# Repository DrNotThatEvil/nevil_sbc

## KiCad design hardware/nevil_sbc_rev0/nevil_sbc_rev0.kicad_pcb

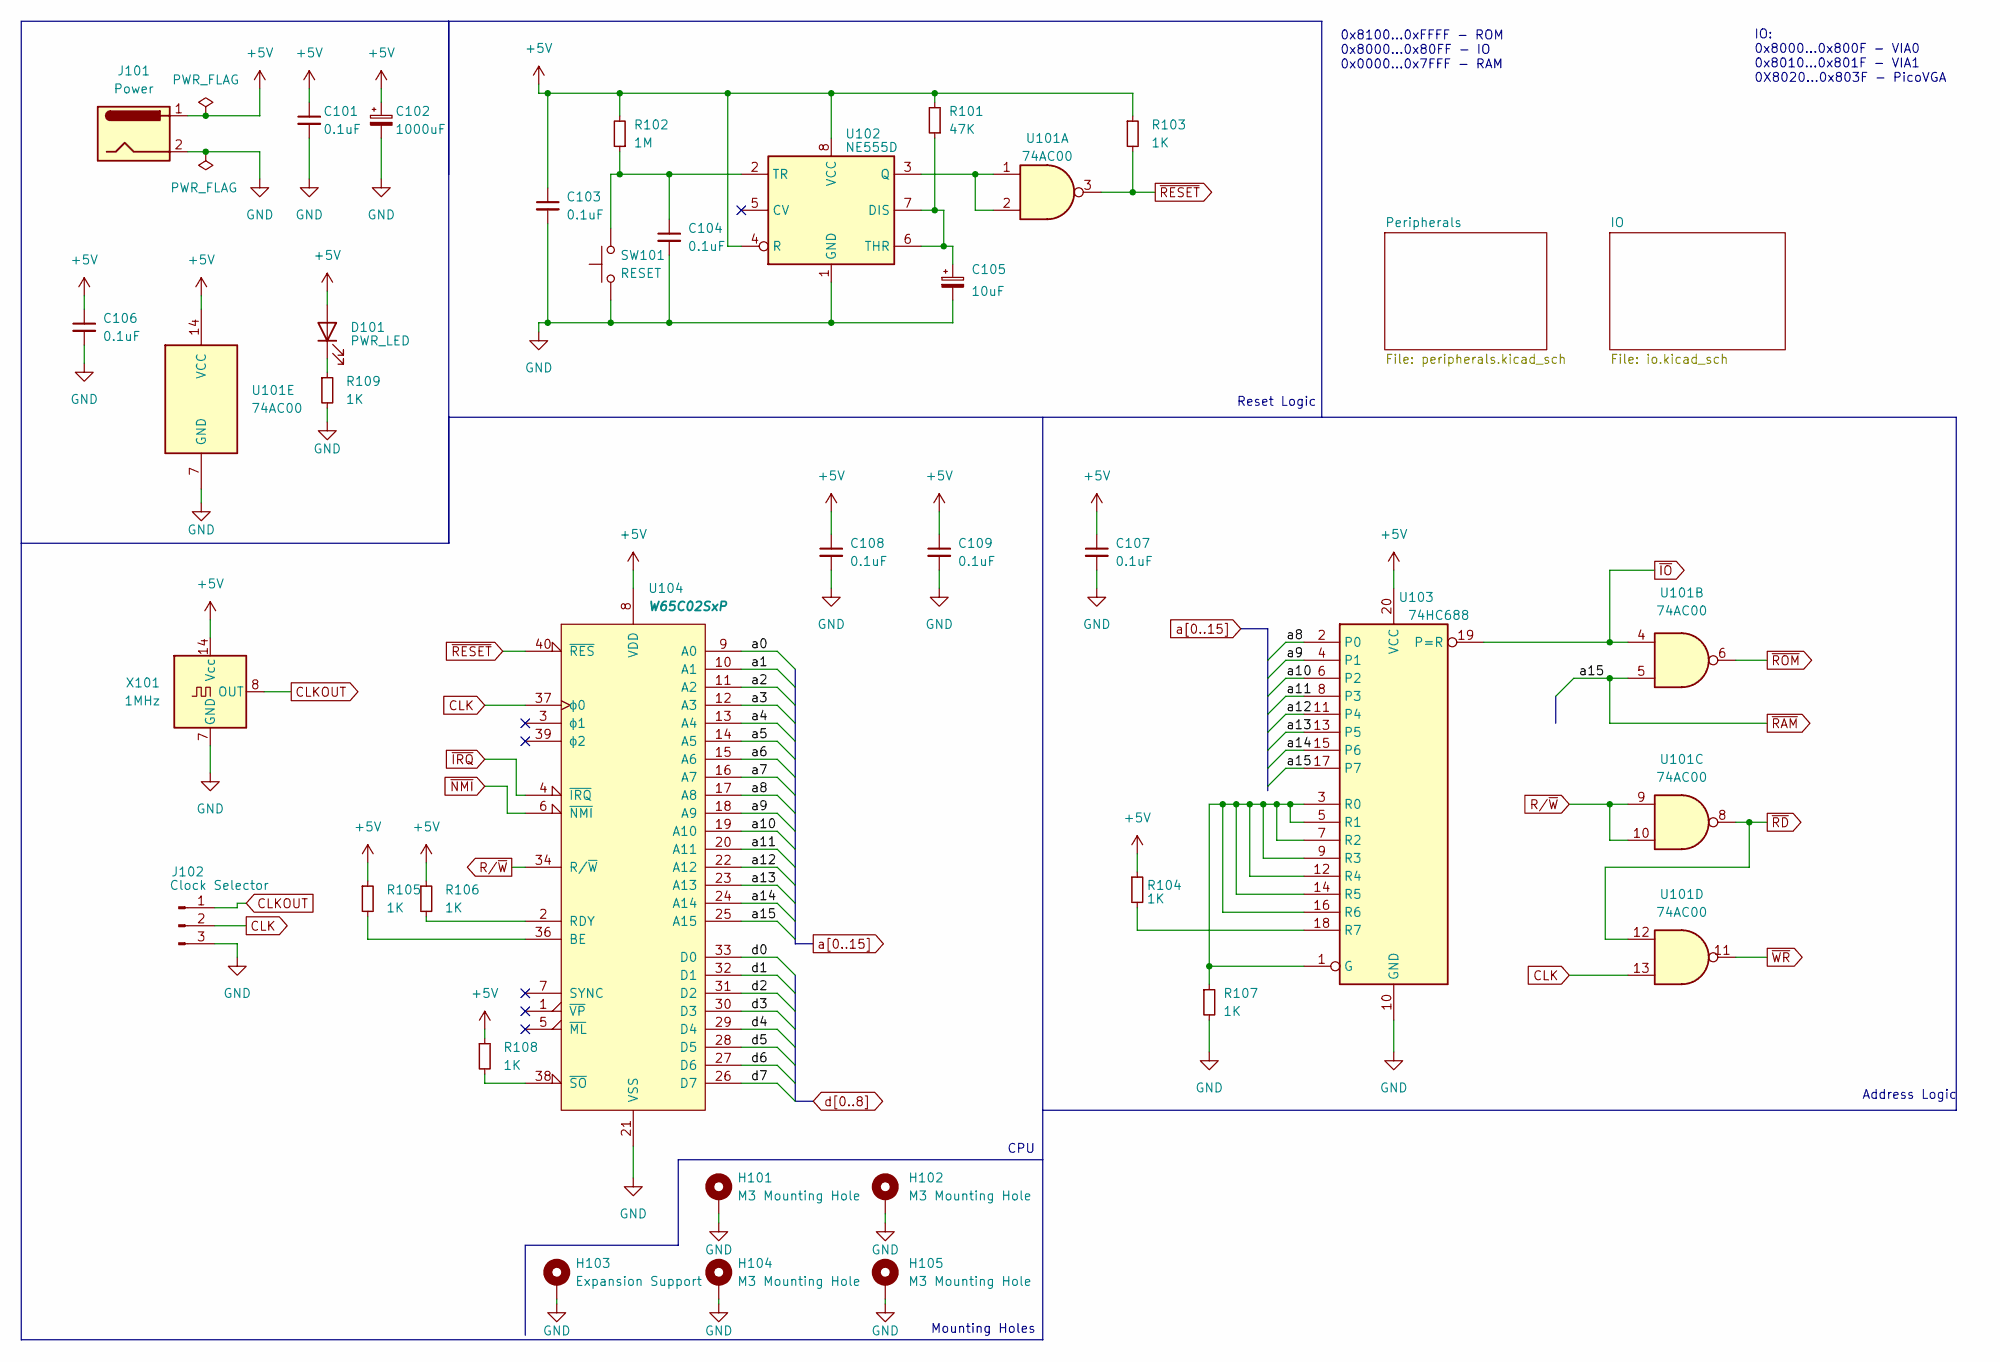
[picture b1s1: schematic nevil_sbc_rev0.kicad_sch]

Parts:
C101, C103, C104, C106, C107, C108, C109: 0.1uF; C_Disc_D5.0mm_W2.5mm_P5.00mm
C102: 1000uF; CP_Radial_D10.0mm_P5.00mm
C105: 10uF; CP_Radial_D5.0mm_P2.00mm
D101: PWR_LED; LED_D3.0mm
H101, H102, H104, H105: M3 Mounting Hole; MountingHole_3.2mm_M3_Pad
H103: Expansion Support; MountingHole_3.2mm_M3_Pad
J101: Power; C9743-CCRNB001R
J102: Clock Selector; PinHeader_1x03_P2.54mm_Vertical
R101: 47K; R_Axial_DIN0204_L3.6mm_D1.6mm_P7.62mm_Horizontal
R102: 1M; R_Axial_DIN0204_L3.6mm_D1.6mm_P7.62mm_Horizontal
R103, R104, R105, R106, R107, R108, R109: 1K; R_Axial_DIN0204_L3.6mm_D1.6mm_P7.62mm_Horizontal
SW101: RESET; SW_PUSH_6mm
U101: 74AC00; DIP-14_W7.62mm_Socket_LongPads
U102: NE555D; SO-8_5.3x6.2mm_P1.27mm
U103: 74HC688; DIP-20_W7.62mm_Socket_LongPads
U104: W65C02SxP; DIP-40_W15.24mm_Socket_LongPads
X101: 1MHz; DIP-14_W7.62mm_Socket_LongPads

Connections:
+5V: C101.1, C102.1, C103.1, C106.1, C107.1, C108.1, C109.1, D101.2 (A), J101.1, R101.2, R102.2, R103.1, R104.1, R105.1, R106.1, R108.1, U101.14 (VCC), U102.4 (R), U102.8 (VCC), U103.20 (VCC), U104.8 (VDD), X101.14 (Vcc); also elsewhere on the board
CLK: J102.2, U101.13, U104.37 (ϕ0); also elsewhere on the board
CLKOUT: J102.1, X101.8 (OUT)
GND: C101.2, C102.2, C103.2, C104.2, C105.2, C106.2, C107.2, C108.2, C109.2, H101.1, H102.1, H103.1, H104.1, H105.1, J101.2, J102.3, R107.2, R109.2, SW101.1, U101.7 (GND), U102.1 (GND), U103.10 (GND), U104.21 (VSS), X101.7 (GND); also elsewhere on the board
unnamed: C104.1, R102.1, SW101.2, U102.2 (TR)
unnamed: C105.1, R101.1, U102.6 (THR), U102.7 (DIS)
unnamed: D101.1 (K), R109.1
unnamed: R104.2, U103.18 (R7)
unnamed: R105.2, U104.36 (BE)
unnamed: R106.2, U104.2 (RDY)
unnamed: R107.1, U103.1 (G), U103.3 (R0), U103.5 (R1), U103.7 (R2), U103.9 (R3), U103.12 (R4), U103.14 (R5), U103.16 (R6)
unnamed: R108.2, U104.38 (~SO)
unnamed: U101.1, U101.2, U102.3 (Q)
R/~W: U101.9, U101.10, U104.34 (R/~W); also elsewhere on the board
a0: U104.9 (A0); also elsewhere on the board
a1: U104.10 (A1); also elsewhere on the board
a2: U104.11 (A2); also elsewhere on the board
a3: U104.12 (A3); also elsewhere on the board
a4: U104.13 (A4); also elsewhere on the board
a5: U104.14 (A5); also elsewhere on the board
a6: U104.15 (A6); also elsewhere on the board
a7: U104.16 (A7); also elsewhere on the board
a8: U103.2 (P0), U104.17 (A8); also elsewhere on the board
a9: U103.4 (P1), U104.18 (A9); also elsewhere on the board
a10: U103.6 (P2), U104.19 (A10); also elsewhere on the board
a11: U103.8 (P3), U104.20 (A11); also elsewhere on the board
a12: U103.11 (P4), U104.22 (A12); also elsewhere on the board
a13: U103.13 (P5), U104.23 (A13); also elsewhere on the board
a14: U103.15 (P6), U104.24 (A14); also elsewhere on the board
d0: U104.33 (D0); also elsewhere on the board
d1: U104.32 (D1); also elsewhere on the board
d2: U104.31 (D2); also elsewhere on the board
d3: U104.30 (D3); also elsewhere on the board
d4: U104.29 (D4); also elsewhere on the board
d5: U104.28 (D5); also elsewhere on the board
d6: U104.27 (D6); also elsewhere on the board
d7: U104.26 (D7); also elsewhere on the board
~IO: U101.4, U103.19 (P=R); also elsewhere on the board
~IRQ: U104.4 (~IRQ); also elsewhere on the board
~NMI: U104.6 (~NMI)
~RAM: U101.5, U103.17 (P7), U104.25 (A15); also elsewhere on the board
~RD: U101.8, U101.12; also elsewhere on the board
~RESET: R103.2, U101.3, U104.40 (~RES); also elsewhere on the board
~ROM: U101.6; also elsewhere on the board
~WR: U101.11; also elsewhere on the board

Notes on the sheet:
CPU
Address Logic
Reset Logic
0x8100...0xFFFF - ROM 0x8000...0x80FF - IO 0x0000...0x7FFF - RAM
IO: 0x8000...0x800F - VIA0 0x8010...0x801F - VIA1 0X8020...0x803F - PicoVGA
Mounting Holes

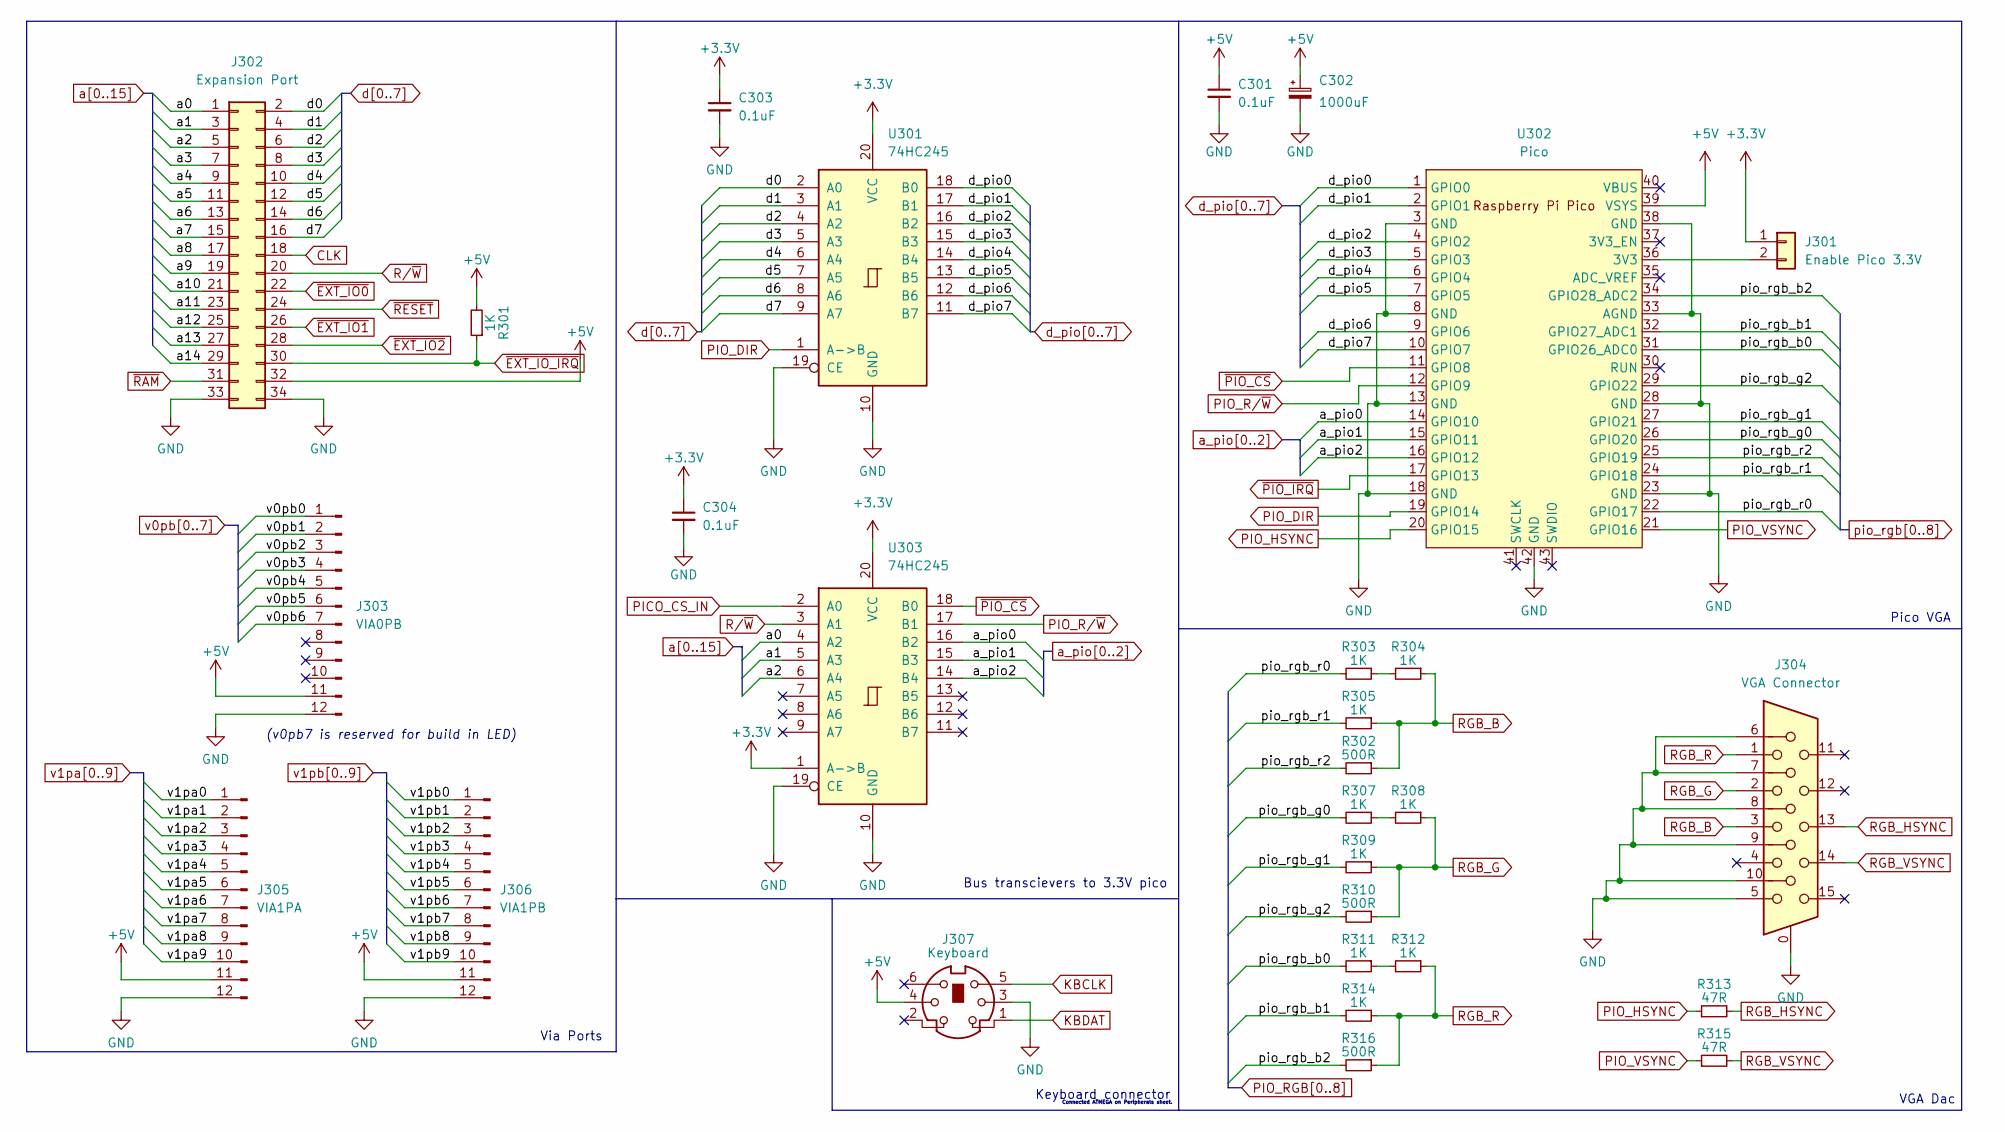
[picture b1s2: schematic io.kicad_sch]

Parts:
C301, C303, C304: 0.1uF; C_Disc_D5.0mm_W2.5mm_P5.00mm
C302: 1000uF; CP_Radial_D10.0mm_P5.00mm
J301: Enable Pico 3.3V; PinHeader_1x02_P2.54mm_Vertical
J302: Expansion Port; PinHeader_2x17_P2.54mm_Vertical
J303: VIA0PB; PinHeader_1x12_P2.54mm_Vertical
J304: VGA Connector; DSUB-15-HD_Female_Horizontal_P2.29x1.98mm_EdgePinOffset8.35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
J305: VIA1PA; PinHeader_1x12_P2.54mm_Vertical
J306: VIA1PB; PinHeader_1x12_P2.54mm_Vertical
J307: Keyboard; TM 0508 A_6
R301, R303, R304, R305, R307, R308, R309, R311, R312, R314: 1K; R_Axial_DIN0204_L3.6mm_D1.6mm_P7.62mm_Horizontal
R302, R310, R316: 500R; R_Axial_DIN0204_L3.6mm_D1.6mm_P7.62mm_Horizontal
R313, R315: 47R; R_Axial_DIN0204_L3.6mm_D1.6mm_P7.62mm_Horizontal
U301, U303: 74HC245; DIP-20_W7.62mm_Socket_LongPads
U302: Pico; RPi_Pico_SMD_TH

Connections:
+3.3V: C303.1, C304.1, J301.1, U301.20 (VCC), U303.1 (A->B), U303.20 (VCC)
+5V: C301.1, C302.1, J302.32, J303.11, J305.11, J306.11, J307.4, R301.2, U302.39 (VSYS); also elsewhere on the board
/IO/pio_rgb_b0: R311.2, U302.31 (GPIO26_ADC0)
/IO/pio_rgb_b1: R314.2, U302.32 (GPIO27_ADC1)
/IO/pio_rgb_b2: R316.2, U302.34 (GPIO28_ADC2)
/IO/pio_rgb_g0: R307.2, U302.26 (GPIO20)
/IO/pio_rgb_g1: R309.2, U302.27 (GPIO21)
/IO/pio_rgb_g2: R310.2, U302.29 (GPIO22)
/IO/pio_rgb_r0: R303.2, U302.22 (GPIO17)
/IO/pio_rgb_r1: R305.2, U302.24 (GPIO18)
/IO/pio_rgb_r2: R302.2, U302.25 (GPIO19)
CLK: J302.18; also elsewhere on the board
GND: C301.2, C302.2, C303.2, C304.2, J302.33, J302.34, J303.12, J304.0, J304.5, J304.6, J304.7, J304.8, J304.9, J304.10, J305.12, J306.12, J307.3, U301.10 (GND), U301.19 (CE), U302.3 (GND), U302.8 (GND), U302.13 (GND), U302.18 (GND), U302.23 (GND), U302.28 (GND), U302.33 (AGND), U302.38 (GND), U302.42 (GND), U303.10 (GND), U303.19 (CE); also elsewhere on the board
KBCLK: J307.5; also elsewhere on the board
KBDAT: J307.1; also elsewhere on the board
unnamed: J301.2, U302.36 (3V3)
unnamed: R303.1, R304.2
unnamed: R307.1, R308.2
unnamed: R311.1, R312.2
PICO_CS_IN: U303.2 (A0); also elsewhere on the board
PIO_DIR: U301.1 (A->B), U302.19 (GPIO14)
PIO_HSYNC: R313.1, U302.20 (GPIO15)
PIO_R/~W: U302.12 (GPIO9), U303.17 (B1)
PIO_VSYNC: R315.1, U302.21 (GPIO16)
RGB_B: J304.3, R302.1, R304.1, R305.1
RGB_G: J304.2, R308.1, R309.1, R310.1
RGB_HSYNC: J304.13, R313.2
RGB_R: J304.1, R312.1, R314.1, R316.1
RGB_VSYNC: J304.14, R315.2
R/~W: J302.20, U303.3 (A1); also elsewhere on the board
a0: J302.1, U303.4 (A2); also elsewhere on the board
a1: J302.3, U303.5 (A3); also elsewhere on the board
a2: J302.5, U303.6 (A4); also elsewhere on the board
a3: J302.7; also elsewhere on the board
a4: J302.9; also elsewhere on the board
a5: J302.11; also elsewhere on the board
a6: J302.13; also elsewhere on the board
a7: J302.15; also elsewhere on the board
a8: J302.17; also elsewhere on the board
a9: J302.19; also elsewhere on the board
a10: J302.21; also elsewhere on the board
a11: J302.23; also elsewhere on the board
a12: J302.25; also elsewhere on the board
a13: J302.27; also elsewhere on the board
a14: J302.29; also elsewhere on the board
a_pio0: U302.14 (GPIO10), U303.16 (B2)
a_pio1: U302.15 (GPIO11), U303.15 (B3)
a_pio2: U302.16 (GPIO12), U303.14 (B4)
d0: J302.2, U301.2 (A0); also elsewhere on the board
d1: J302.4, U301.3 (A1); also elsewhere on the board
d2: J302.6, U301.4 (A2); also elsewhere on the board
d3: J302.8, U301.5 (A3); also elsewhere on the board
d4: J302.10, U301.6 (A4); also elsewhere on the board
d5: J302.12, U301.7 (A5); also elsewhere on the board
d6: J302.14, U301.8 (A6); also elsewhere on the board
d7: J302.16, U301.9 (A7); also elsewhere on the board
d_pio0: U301.18 (B0), U302.1 (GPIO0)
d_pio1: U301.17 (B1), U302.2 (GPIO1)
d_pio2: U301.16 (B2), U302.4 (GPIO2)
d_pio3: U301.15 (B3), U302.5 (GPIO3)
d_pio4: U301.14 (B4), U302.6 (GPIO4)
d_pio5: U301.13 (B5), U302.7 (GPIO5)
d_pio6: U301.12 (B6), U302.9 (GPIO6)
d_pio7: U301.11 (B7), U302.10 (GPIO7)
v0pb0: J303.1; also elsewhere on the board
v0pb1: J303.2; also elsewhere on the board
v0pb2: J303.3; also elsewhere on the board
v0pb3: J303.4; also elsewhere on the board
v0pb4: J303.5; also elsewhere on the board
v0pb5: J303.6; also elsewhere on the board
v0pb6: J303.7; also elsewhere on the board
v1pa0: J305.1; also elsewhere on the board
v1pa1: J305.2; also elsewhere on the board
v1pa2: J305.3; also elsewhere on the board
v1pa3: J305.4; also elsewhere on the board
v1pa4: J305.5; also elsewhere on the board
v1pa5: J305.6; also elsewhere on the board
v1pa6: J305.7; also elsewhere on the board
v1pa7: J305.8; also elsewhere on the board
v1pa8: J305.9; also elsewhere on the board
v1pa9: J305.10; also elsewhere on the board
v1pb0: J306.1; also elsewhere on the board
v1pb1: J306.2; also elsewhere on the board
v1pb2: J306.3; also elsewhere on the board
v1pb3: J306.4; also elsewhere on the board
v1pb4: J306.5; also elsewhere on the board
v1pb5: J306.6; also elsewhere on the board
v1pb6: J306.7; also elsewhere on the board
v1pb7: J306.8; also elsewhere on the board
v1pb8: J306.9; also elsewhere on the board
v1pb9: J306.10; also elsewhere on the board
~EXT_IO0: J302.22; also elsewhere on the board
~EXT_IO1: J302.26; also elsewhere on the board
~EXT_IO2: J302.28; also elsewhere on the board
~EXT_IO_IRQ: J302.30, R301.1; also elsewhere on the board
~PIO_CS: U302.11 (GPIO8), U303.18 (B0)
~PIO_IRQ: U302.17 (GPIO13)
~RAM: J302.31; also elsewhere on the board
~RESET: J302.24; also elsewhere on the board

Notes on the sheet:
Bus transcievers to 3.3V pico
VGA Dac
Connected ATMEGA on Peripherals sheet.
Via Ports
Keyboard connector
Pico VGA
(v0pb7 is reserved for build in LED)

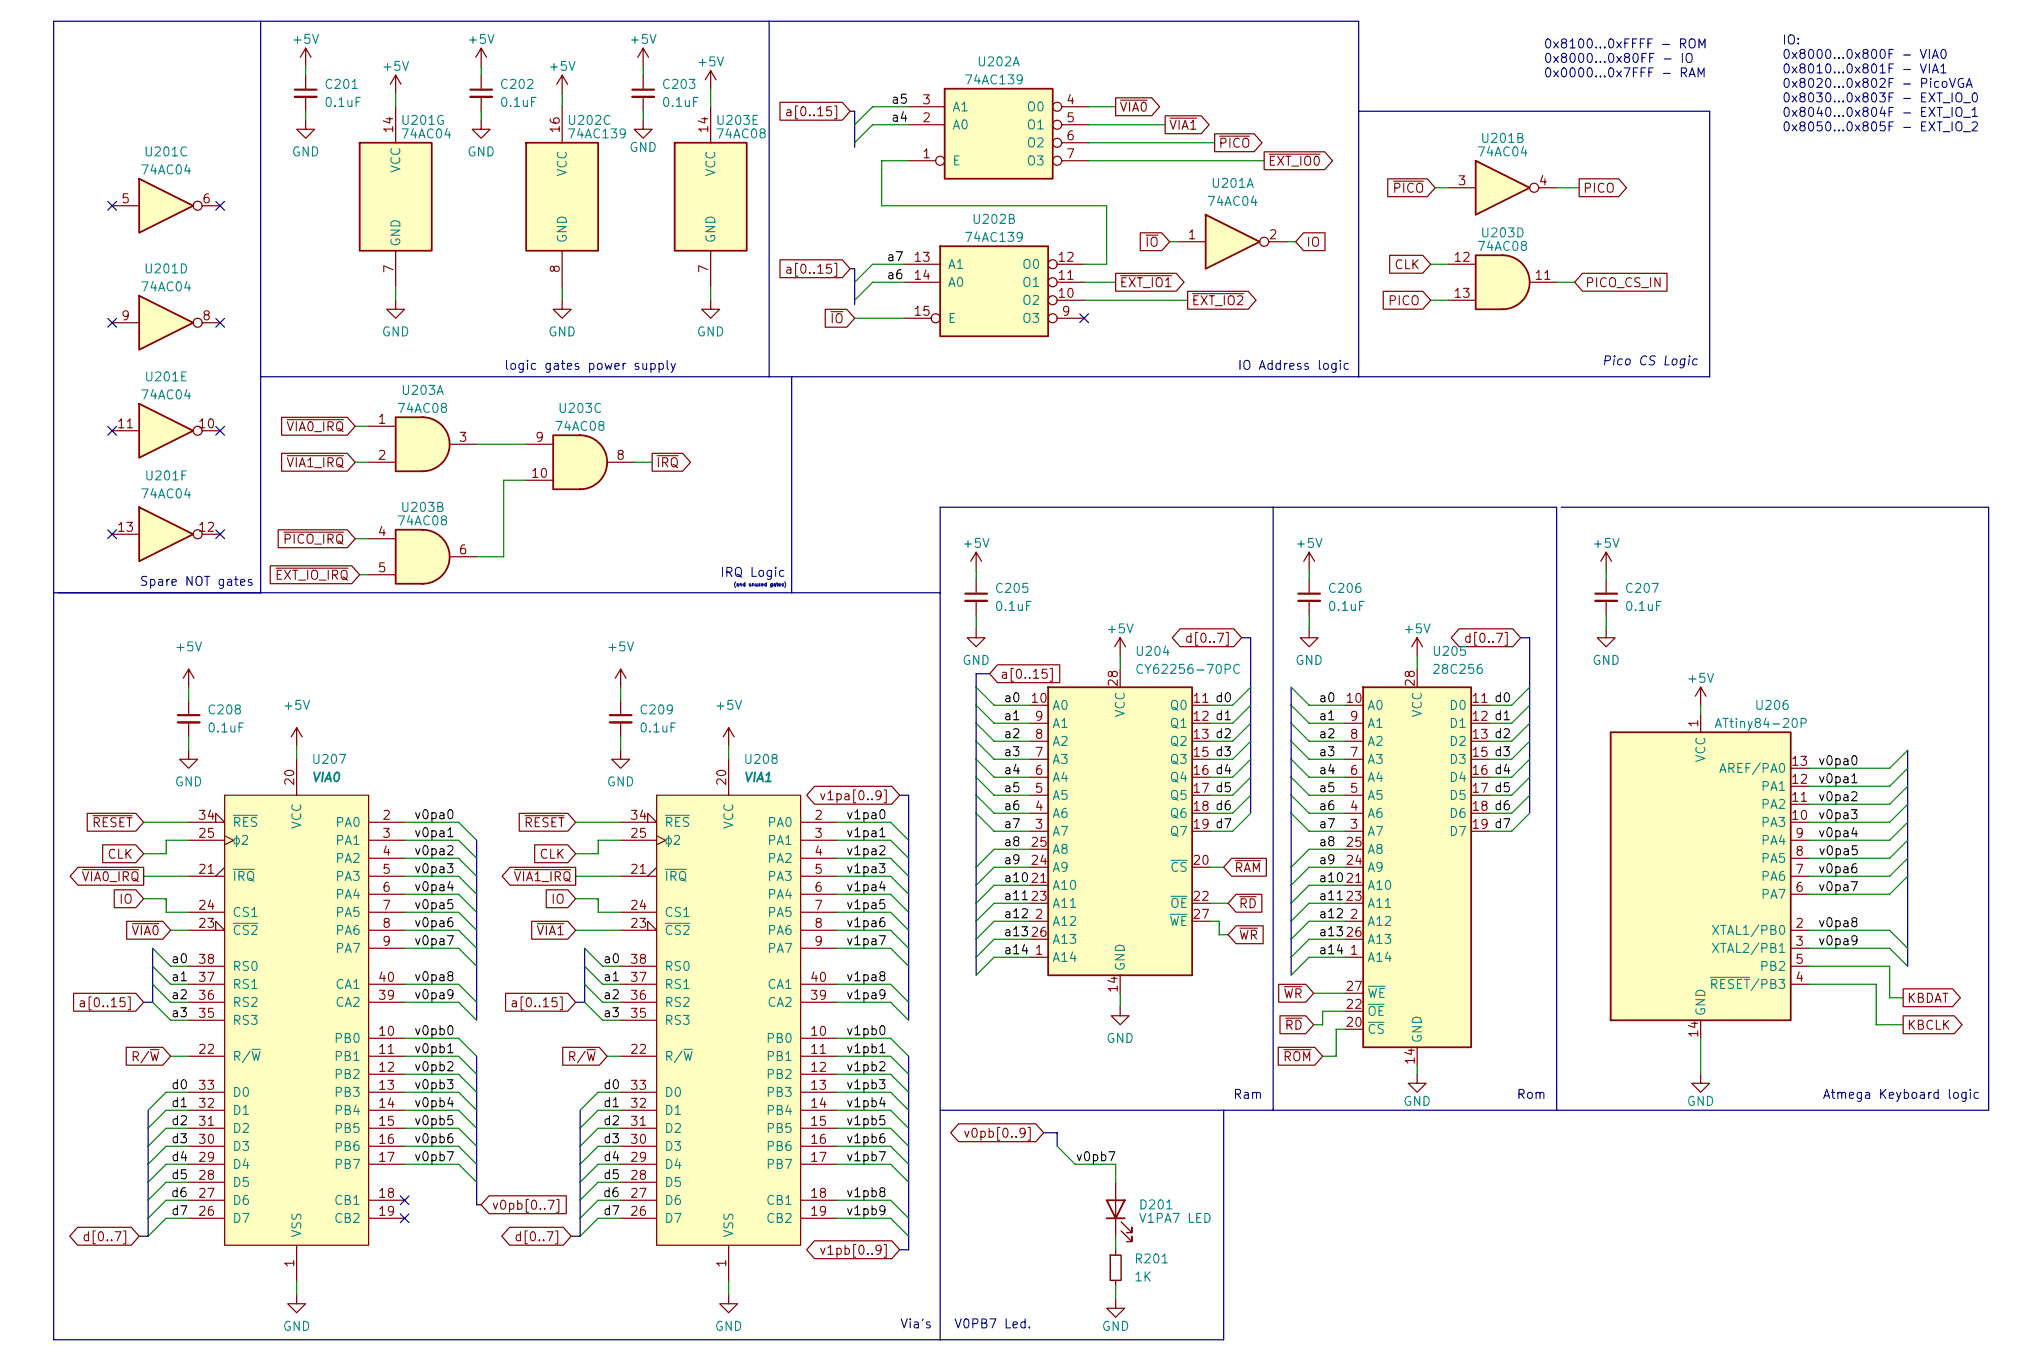
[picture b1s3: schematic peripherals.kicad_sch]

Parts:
C201, C202, C203, C205, C206, C207, C208, C209: 0.1uF; C_Disc_D5.0mm_W2.5mm_P5.00mm
D201: V1PA7 LED; LED_D3.0mm
R201: 1K; R_Axial_DIN0204_L3.6mm_D1.6mm_P7.62mm_Horizontal
U201: 74AC04; DIP-14_W7.62mm_Socket_LongPads
U202: 74AC139; TSSOP-16_4.4x5mm_P0.65mm
U203: 74AC08; DIP-14_W7.62mm_Socket_LongPads
U204: CY62256-70PC; DIP-28_W15.24mm_Socket_LongPads
U205: 28C256; DIP-28_W15.24mm_Socket_LongPads
U206: ATtiny84-20P; DIP-14_W7.62mm
U207: VIA0; DIP-40_W15.24mm_Socket_LongPads
U208: VIA1; DIP-40_W15.24mm_Socket_LongPads

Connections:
+5V: C201.1, C202.1, C203.1, C205.1, C206.1, C207.1, C208.1, C209.1, U201.14 (VCC), U202.16 (VCC), U203.14 (VCC), U204.28 (VCC), U205.28 (VCC), U206.1 (VCC), U207.20 (VCC), U208.20 (VCC); also elsewhere on the board
/Peripherals/v0pa0: U206.13 (AREF/PA0), U207.2 (PA0)
/Peripherals/v0pa1: U206.12 (PA1), U207.3 (PA1)
/Peripherals/v0pa2: U206.11 (PA2), U207.4 (PA2)
/Peripherals/v0pa3: U206.10 (PA3), U207.5 (PA3)
/Peripherals/v0pa4: U206.9 (PA4), U207.6 (PA4)
/Peripherals/v0pa5: U206.8 (PA5), U207.7 (PA5)
/Peripherals/v0pa6: U206.7 (PA6), U207.8 (PA6)
/Peripherals/v0pa7: U206.6 (PA7), U207.9 (PA7)
/Peripherals/v0pa8: U206.2 (XTAL1/PB0), U207.40 (CA1)
/Peripherals/v0pa9: U206.3 (XTAL2/PB1), U207.39 (CA2)
CLK: U203.12, U207.25 (ϕ2), U208.25 (ϕ2); also elsewhere on the board
GND: C201.2, C202.2, C203.2, C205.2, C206.2, C207.2, C208.2, C209.2, R201.2, U201.7 (GND), U202.8 (GND), U203.7 (GND), U204.14 (GND), U205.14 (GND), U206.14 (GND), U207.1 (VSS), U208.1 (VSS); also elsewhere on the board
IO: U201.2, U207.24 (CS1), U208.24 (CS1)
KBCLK: U206.4 (~RESET/PB3); also elsewhere on the board
KBDAT: U206.5 (PB2); also elsewhere on the board
unnamed: D201.1 (K), R201.1
unnamed: U202.1 (E), U202.12 (O0)
unnamed: U203.3, U203.9
unnamed: U203.6, U203.10
PICO: U201.4, U203.13
PICO_CS_IN: U203.11; also elsewhere on the board
R/~W: U207.22 (R/~W), U208.22 (R/~W); also elsewhere on the board
a0: U204.10 (A0), U205.10 (A0), U207.38 (RS0), U208.38 (RS0); also elsewhere on the board
a1: U204.9 (A1), U205.9 (A1), U207.37 (RS1), U208.37 (RS1); also elsewhere on the board
a2: U204.8 (A2), U205.8 (A2), U207.36 (RS2), U208.36 (RS2); also elsewhere on the board
a3: U204.7 (A3), U205.7 (A3), U207.35 (RS3), U208.35 (RS3); also elsewhere on the board
a4: U202.2 (A0), U204.6 (A4), U205.6 (A4); also elsewhere on the board
a5: U202.3 (A1), U204.5 (A5), U205.5 (A5); also elsewhere on the board
a6: U202.14 (A0), U204.4 (A6), U205.4 (A6); also elsewhere on the board
a7: U202.13 (A1), U204.3 (A7), U205.3 (A7); also elsewhere on the board
a8: U204.25 (A8), U205.25 (A8); also elsewhere on the board
a9: U204.24 (A9), U205.24 (A9); also elsewhere on the board
a10: U204.21 (A10), U205.21 (A10); also elsewhere on the board
a11: U204.23 (A11), U205.23 (A11); also elsewhere on the board
a12: U204.2 (A12), U205.2 (A12); also elsewhere on the board
a13: U204.26 (A13), U205.26 (A13); also elsewhere on the board
a14: U204.1 (A14), U205.1 (A14); also elsewhere on the board
d0: U204.11 (Q0), U205.11 (D0), U207.33 (D0), U208.33 (D0); also elsewhere on the board
d1: U204.12 (Q1), U205.12 (D1), U207.32 (D1), U208.32 (D1); also elsewhere on the board
d2: U204.13 (Q2), U205.13 (D2), U207.31 (D2), U208.31 (D2); also elsewhere on the board
d3: U204.15 (Q3), U205.15 (D3), U207.30 (D3), U208.30 (D3); also elsewhere on the board
d4: U204.16 (Q4), U205.16 (D4), U207.29 (D4), U208.29 (D4); also elsewhere on the board
d5: U204.17 (Q5), U205.17 (D5), U207.28 (D5), U208.28 (D5); also elsewhere on the board
d6: U204.18 (Q6), U205.18 (D6), U207.27 (D6), U208.27 (D6); also elsewhere on the board
d7: U204.19 (Q7), U205.19 (D7), U207.26 (D7), U208.26 (D7); also elsewhere on the board
v0pb0: U207.10 (PB0); also elsewhere on the board
v0pb1: U207.11 (PB1); also elsewhere on the board
v0pb2: U207.12 (PB2); also elsewhere on the board
v0pb3: U207.13 (PB3); also elsewhere on the board
v0pb4: U207.14 (PB4); also elsewhere on the board
v0pb5: U207.15 (PB5); also elsewhere on the board
v0pb6: U207.16 (PB6); also elsewhere on the board
v0pb7: D201.2 (A), U207.17 (PB7)
v1pa0: U208.2 (PA0); also elsewhere on the board
v1pa1: U208.3 (PA1); also elsewhere on the board
v1pa2: U208.4 (PA2); also elsewhere on the board
v1pa3: U208.5 (PA3); also elsewhere on the board
v1pa4: U208.6 (PA4); also elsewhere on the board
v1pa5: U208.7 (PA5); also elsewhere on the board
v1pa6: U208.8 (PA6); also elsewhere on the board
v1pa7: U208.9 (PA7); also elsewhere on the board
v1pa8: U208.40 (CA1); also elsewhere on the board
v1pa9: U208.39 (CA2); also elsewhere on the board
v1pb0: U208.10 (PB0); also elsewhere on the board
v1pb1: U208.11 (PB1); also elsewhere on the board
v1pb2: U208.12 (PB2); also elsewhere on the board
v1pb3: U208.13 (PB3); also elsewhere on the board
v1pb4: U208.14 (PB4); also elsewhere on the board
v1pb5: U208.15 (PB5); also elsewhere on the board
v1pb6: U208.16 (PB6); also elsewhere on the board
v1pb7: U208.17 (PB7); also elsewhere on the board
v1pb8: U208.18 (CB1); also elsewhere on the board
v1pb9: U208.19 (CB2); also elsewhere on the board
~EXT_IO0: U202.7 (O3); also elsewhere on the board
~EXT_IO1: U202.11 (O1); also elsewhere on the board
~EXT_IO2: U202.10 (O2); also elsewhere on the board
~EXT_IO_IRQ: U203.5; also elsewhere on the board
~IO: U201.1, U202.15 (E); also elsewhere on the board
~IRQ: U203.8; also elsewhere on the board
~PICO_IRQ: U203.4
~PICO: U201.3, U202.6 (O2)
~RAM: U204.20 (~CS); also elsewhere on the board
~RD: U204.22 (~OE), U205.22 (~OE); also elsewhere on the board
~RESET: U207.34 (~RES), U208.34 (~RES); also elsewhere on the board
~ROM: U205.20 (~CS); also elsewhere on the board
~VIA0_IRQ: U203.1, U207.21 (~IRQ)
~VIA0: U202.4 (O0), U207.23 (~CS2)
~VIA1_IRQ: U203.2, U208.21 (~IRQ)
~VIA1: U202.5 (O1), U208.23 (~CS2)
~WR: U204.27 (~WE), U205.27 (~WE); also elsewhere on the board

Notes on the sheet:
Spare NOT gates
(and unused gates)
logic gates power supply
0x8100...0xFFFF - ROM 0x8000...0x80FF - IO 0x0000...0x7FFF - RAM
Rom
Via's
Pico CS Logic
V0PB7 Led.
Ram
IRQ Logic
IO: 0x8000...0x800F - VIA0 0x8010...0x801F - VIA1 0x8020...0x802F - PicoVGA 0x8030...0x803F - EXT_IO_0 0x8040...0x804F - EXT_IO_1 0x8050...0x805F - EXT_IO_2
Atmega Keyboard logic
IO Address logic

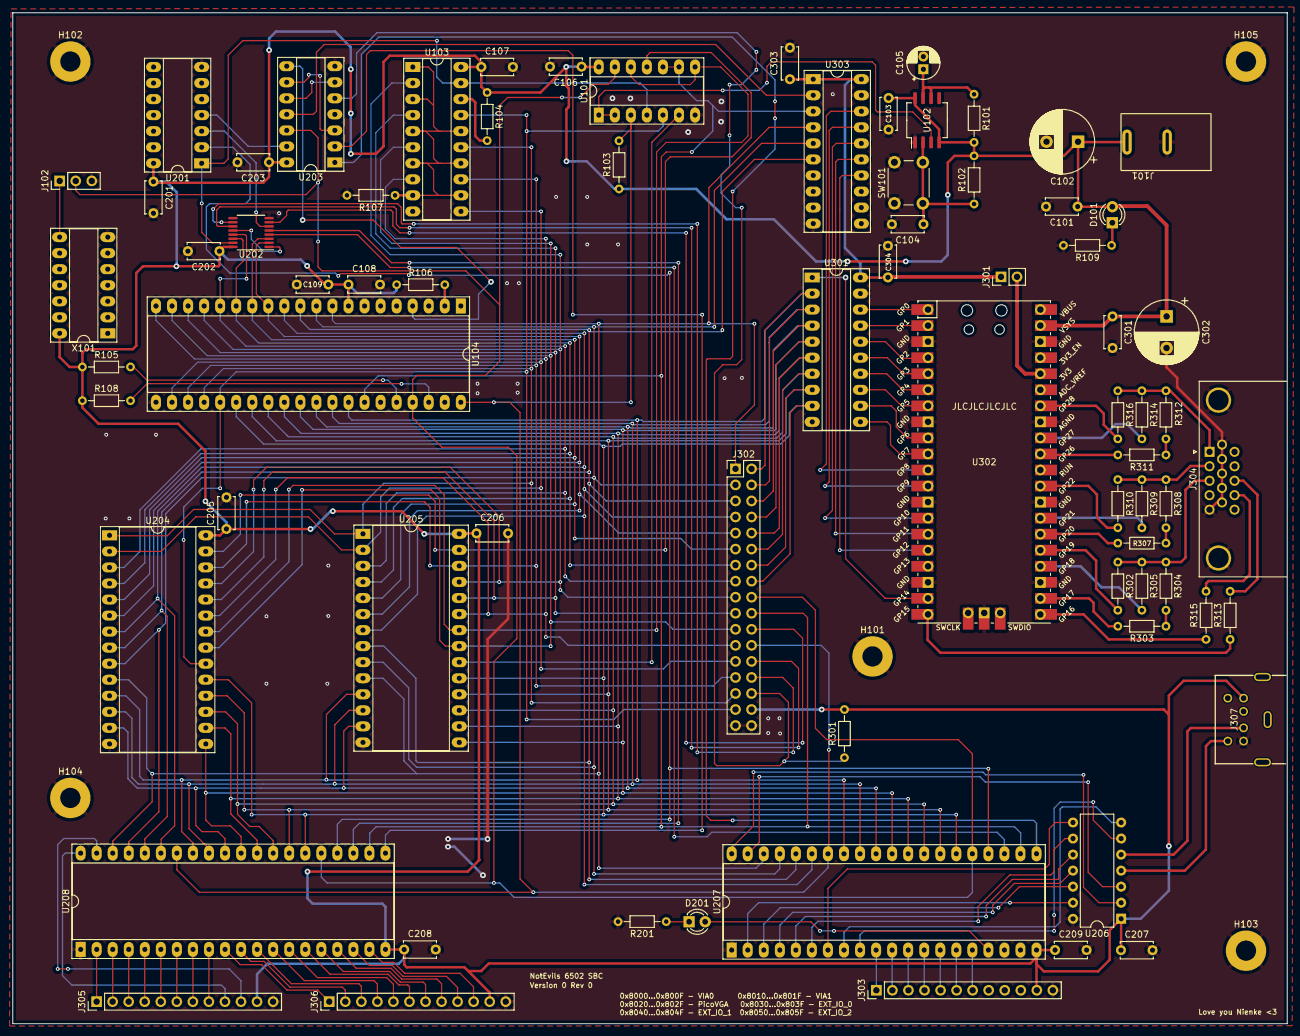
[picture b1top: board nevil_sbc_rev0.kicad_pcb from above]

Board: 2 copper layers, 201.8 x 160.0 mm, 79 parts (0 on the bottom side), 135 nets.

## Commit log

2022-09-13 add resources to help
2022-09-14 Working on base 6502 bus for pico vga
2022-09-15 WIP: Working on bus
2022-09-23 Hardware schematics
2022-09-25 Updating schematics
2022-10-06 Stashing work to switch machines
2022-10-07 Stashing work
2022-10-09 Stashing work to continue on workstation
2022-10-20 Finsing up peripherals almost done with schematic
2022-10-22 Finishing base schematic
2022-10-25 Add pcb files and small clk change for pico
2022-10-25 Working on pcb
2022-10-25 Update pcb
2022-10-25 Working on PCB address bus
2022-11-04 working on vga code
2022-11-04 Switching to desktop
2022-11-12 Pushing for real pcb work
2022-11-21 Added small txt to keep track of bugs
